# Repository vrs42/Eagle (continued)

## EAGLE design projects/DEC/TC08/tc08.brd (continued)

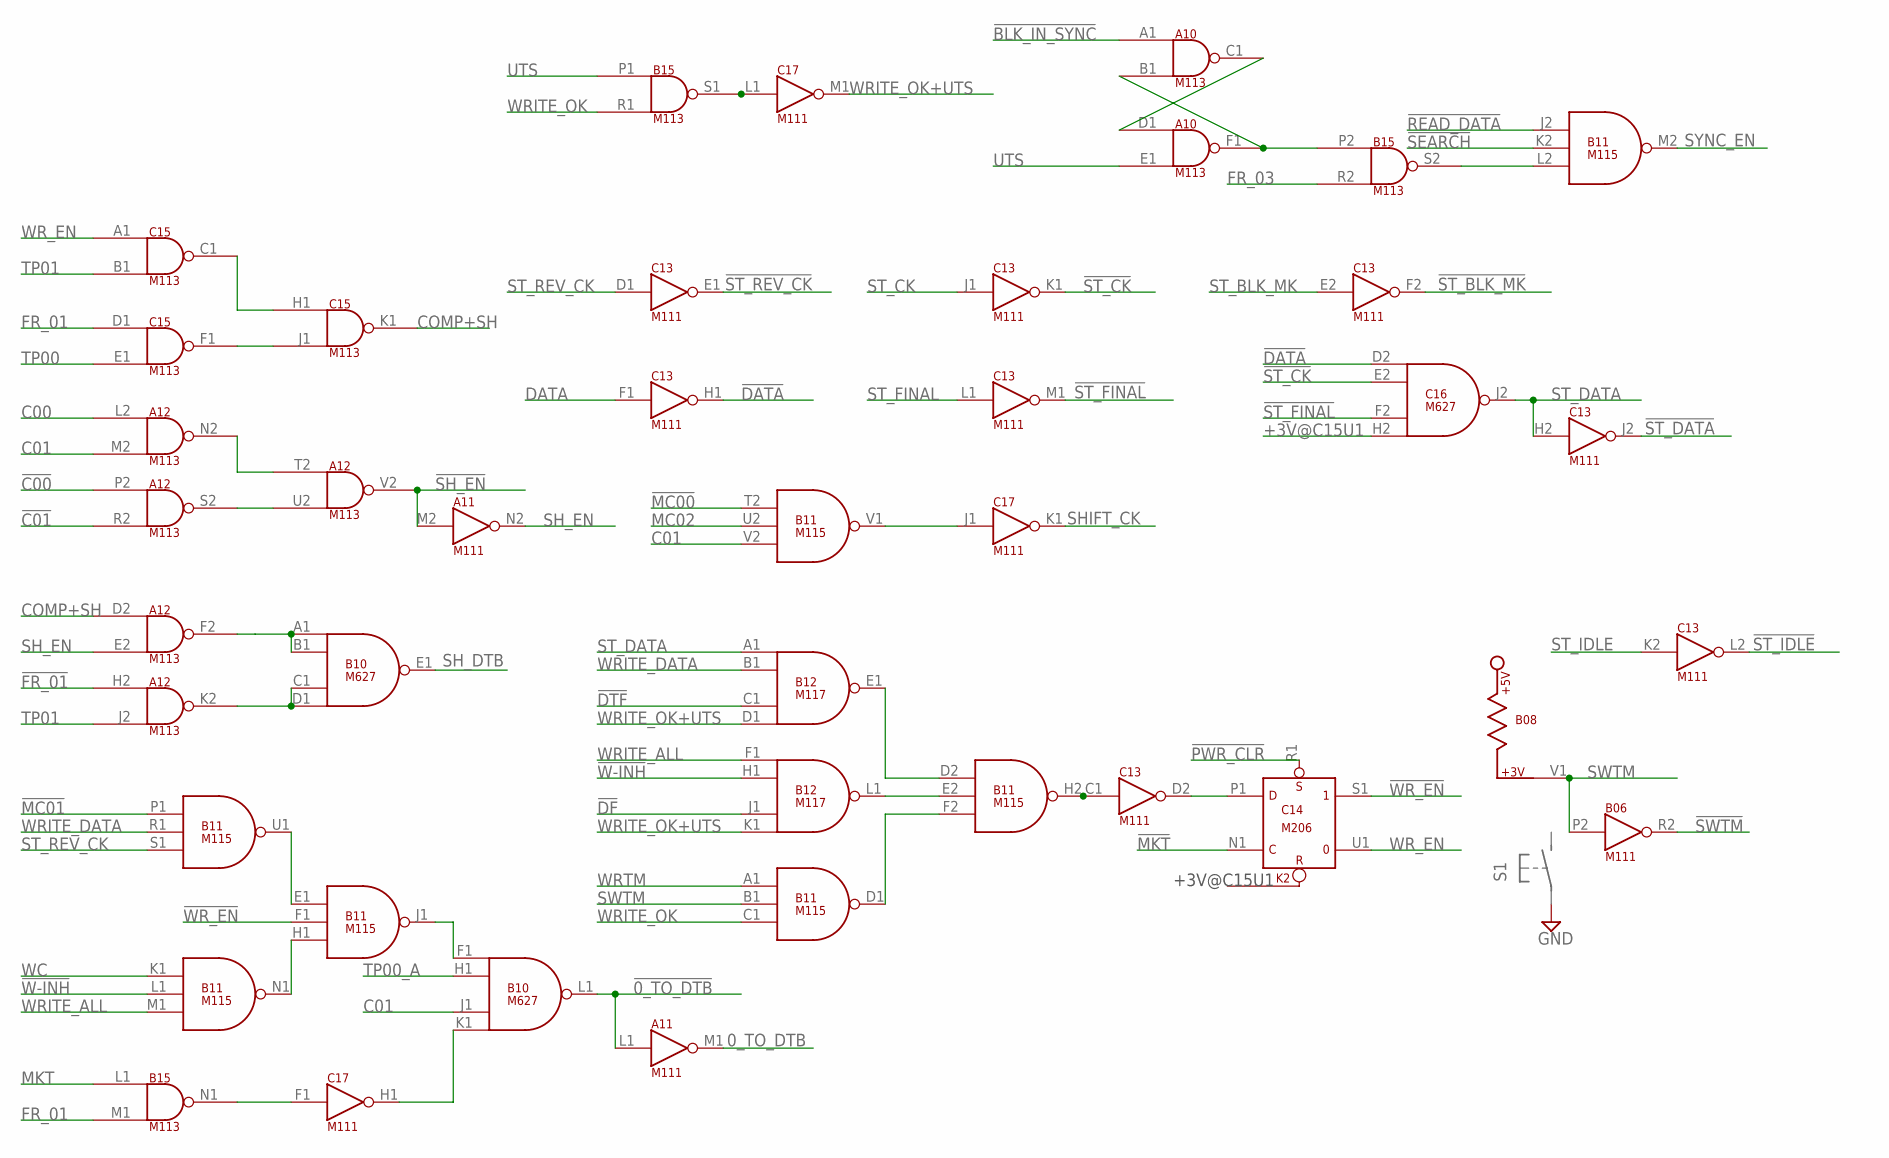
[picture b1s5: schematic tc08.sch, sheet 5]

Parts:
A10, A12: M113; H807
A11: M111; H807
B06: M111; H807
B08, B15: M113; H807
B10: M627; H807
B11: M115; H807
B12: M117; H807
C13, C17: M111; H807
C14: M206; H807
C15: M113; H807
C16: M627; H807

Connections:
0_TO_DTB: A11.M1 (OUT); also elsewhere on the board
!0_TO_DTB: A11.L1 (IN), B10.L1 (OUT); also elsewhere on the board
!BLK_IN_SYNC: A10.A1 (IN1); also elsewhere on the board
!C00: A12.P2 (IN1); also elsewhere on the board
!C01: A12.R2 (IN2); also elsewhere on the board
!DATA: C13.H1 (OUT), C16.D2 (IN1); also elsewhere on the board
!DF: B12.J1 (IN3); also elsewhere on the board
!DTF: B12.C1 (IN3); also elsewhere on the board
!FR_01: A12.H2 (IN1); also elsewhere on the board
!MC00: B11.T2 (IN1); also elsewhere on the board
!MC01: B11.P1 (IN1); also elsewhere on the board
!MKT: C14.N1 (C); also elsewhere on the board
!PWR_CLR: C14.R1 (S); also elsewhere on the board
!READ_DATA: B11.J2 (IN1); also elsewhere on the board
!SEARCH: B11.K2 (IN2); also elsewhere on the board
!SH_EN: A11.M2 (IN), A12.V2 (OUT); also elsewhere on the board
!ST_BLK_MK: C13.F2 (OUT); also elsewhere on the board
!ST_CK: C13.K1 (OUT), C16.E2 (IN2)
!ST_DATA: C13.J2 (OUT)
!ST_FINAL: C13.M1 (OUT), C16.F2 (IN3); also elsewhere on the board
!ST_IDLE: C13.L2 (OUT); also elsewhere on the board
!ST_REV_CK: C13.E1 (OUT)
!SWTM: B06.R2 (OUT); also elsewhere on the board
!W-INH: B11.L1 (IN2), B12.H1 (IN2); also elsewhere on the board
!WR_EN: B11.F1 (IN2), C14.S1 (1); also elsewhere on the board
+3V@C15U1: C16.H2 (IN4); also elsewhere on the board
C00: A12.L2 (IN1); also elsewhere on the board
C01: A12.M2 (IN2), B10.J1 (IN3), B11.V2 (IN3); also elsewhere on the board
COMP+SH: A12.D2 (IN1), C15.K1 (OUT); also elsewhere on the board
DATA: C13.F1 (IN); also elsewhere on the board
FR_01: B15.M1 (IN2), C15.D1 (IN1); also elsewhere on the board
FR_03: B15.R2 (IN2); also elsewhere on the board
GND: A10.C2 (GND), A10.T1 (GND), A11.C2 (GND), A11.T1 (GND), A12.C2 (GND), A12.T1 (GND), B06.C2 (GND), B06.T1 (GND), B08.C2 (GND), B08.T1 (GND), B10.C2 (GND), B10.T1 (GND), B11.C2 (GND), B11.T1 (GND), B12.C2 (GND), B12.T1 (GND), B15.C2 (GND), B15.T1 (GND), C13.C2 (GND), C13.T1 (GND), C14.C2 (GND), C14.T1 (GND), C15.C2 (GND), C15.T1 (GND), C16.C2 (GND), C16.T1 (GND), C17.C2 (GND), C17.T1 (GND); also elsewhere on the board
MC02: B11.U2 (IN2); also elsewhere on the board
MKT: B15.L1 (IN1); also elsewhere on the board
unnamed: B15.S1 (OUT), C17.L1 (IN)
unnamed: C13.D2 (OUT), C14.P1 (D)
unnamed: C15.C1 (OUT), C15.H1 (IN1)
unnamed: C15.F1 (OUT), C15.J1 (IN2)
unnamed: A12.N2 (OUT), A12.T2 (IN1)
unnamed: A12.S2 (OUT), A12.U2 (IN2)
unnamed: B11.H2 (OUT), C13.C1 (IN)
unnamed: B11.E2 (IN2), B12.L1 (OUT)
unnamed: B11.D2 (IN1), B12.E1 (OUT)
unnamed: B11.D1 (OUT), B11.F2 (IN3)
unnamed: A12.K2 (OUT), B10.C1 (IN3), B10.D1 (IN4)
unnamed: A12.F2 (OUT), B10.A1 (IN1), B10.B1 (IN2)
unnamed: B11.E1 (IN1), B11.U1 (OUT)
unnamed: B15.N1 (OUT), C17.F1 (IN)
unnamed: B11.H1 (IN3), B11.N1 (OUT)
unnamed: B10.F1 (IN1), B11.J1 (OUT)
unnamed: B10.K1 (IN4), C17.H1 (OUT)
unnamed: B11.V1 (OUT), C17.J1 (IN)
unnamed: A10.C1 (OUT), A10.D1 (IN1)
unnamed: A10.B1 (IN2), A10.F1 (OUT), B15.P2 (IN1)
unnamed: B11.L2 (IN3), B15.S2 (OUT)
SHIFT_CK: C17.K1 (OUT); also elsewhere on the board
SH_DTB: B10.E1 (OUT); also elsewhere on the board
SH_EN: A11.N2 (OUT), A12.E2 (IN2); also elsewhere on the board
ST_BLK_MK: C13.E2 (IN); also elsewhere on the board
ST_CK: C13.J1 (IN); also elsewhere on the board
ST_DATA: B12.A1 (IN1), C13.H2 (IN), C16.J2 (OUT)
ST_FINAL: C13.L1 (IN); also elsewhere on the board
ST_IDLE: C13.K2 (IN); also elsewhere on the board
ST_REV_CK: B11.S1 (IN3), C13.D1 (IN); also elsewhere on the board
SWTM: B06.P2 (IN), B08.V1, B11.B1 (IN2); also elsewhere on the board
SYNC_EN: B11.M2 (OUT); also elsewhere on the board
TP00: C15.E1 (IN2); also elsewhere on the board
TP00_A: B10.H1 (IN2); also elsewhere on the board
TP01: A12.J2 (IN2), C15.B1 (IN2); also elsewhere on the board
UTS: A10.E1 (IN2), B15.P1 (IN1); also elsewhere on the board
VCC: A10.A2 (VCC), A11.A2 (VCC), A12.A2 (VCC), B06.A2 (VCC), B08.A2 (VCC), B10.A2 (VCC), B11.A2 (VCC), B12.A2 (VCC), B15.A2 (VCC), C13.A2 (VCC), C14.A2 (VCC), C15.A2 (VCC), C16.A2 (VCC), C17.A2 (VCC); also elsewhere on the board
WC: B11.K1 (IN1); also elsewhere on the board
WRITE_ALL: B11.M1 (IN3), B12.F1 (IN1); also elsewhere on the board
WRITE_DATA: B11.R1 (IN2), B12.B1 (IN2); also elsewhere on the board
WRITE_OK: B11.C1 (IN3), B15.R1 (IN2); also elsewhere on the board
WRITE_OK+UTS: B12.D1 (IN4), B12.K1 (IN4), C17.M1 (OUT)
WRTM: B11.A1 (IN1); also elsewhere on the board
WR_EN: C14.U1 (0), C15.A1 (IN1); also elsewhere on the board

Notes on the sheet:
+3V@C15U1

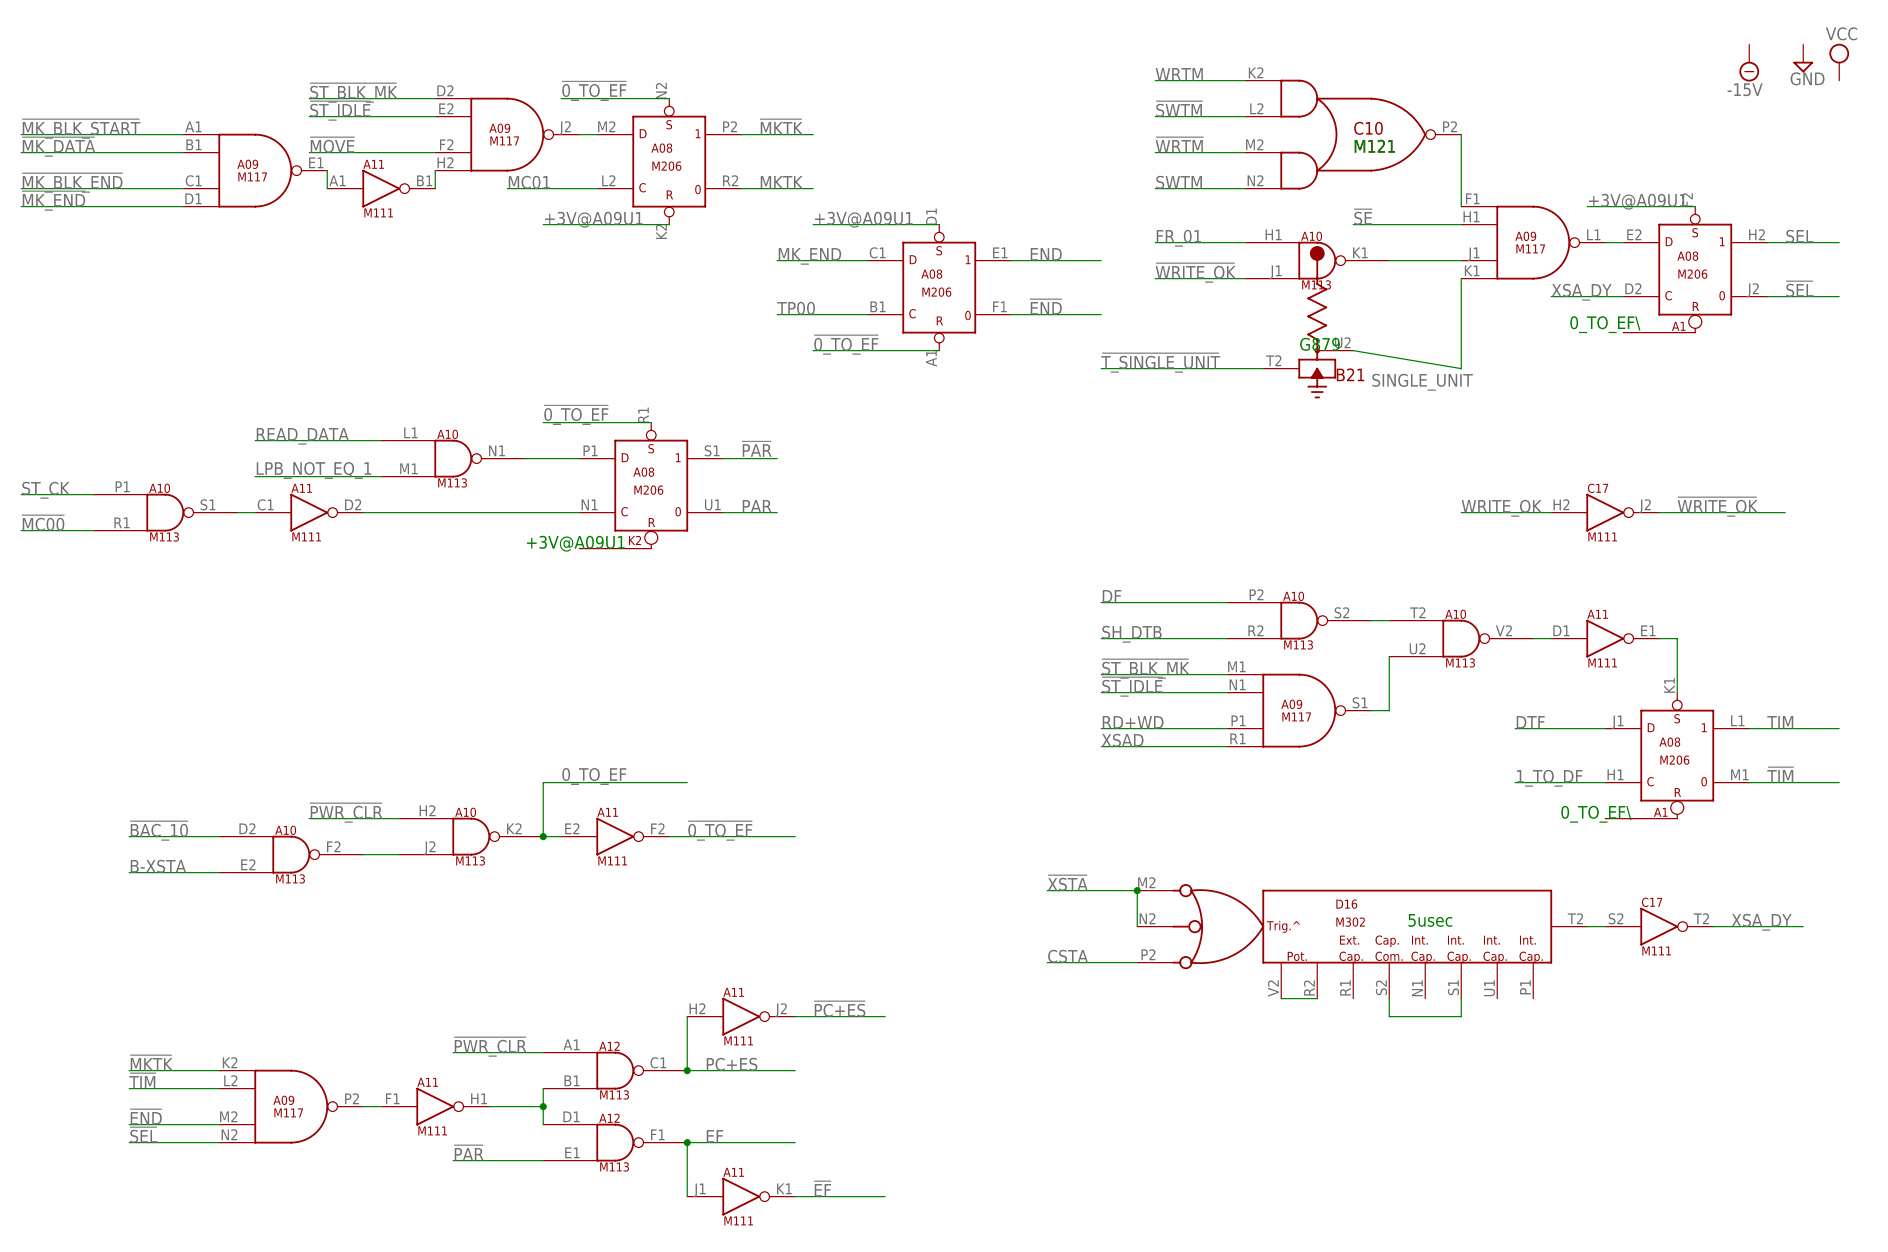
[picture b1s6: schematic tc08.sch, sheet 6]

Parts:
A08: M206; H807
A09: M117; H807
A10, A12: M113; H807
A11: M111; H807
B21: G879; H807
C10: M121; H807
C17: M111; H807
D16: M302; H807

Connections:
0_TO_EF: A10.K2 (OUT), A11.E2 (IN)
1_TO_DF: A08.H1 (C); also elsewhere on the board
!0_TO_EF: A08.A1 (R), A08.N2 (S), A08.R1 (S), A11.F2 (OUT)
!BAC_10: A10.D2 (IN1); also elsewhere on the board
!EF: A11.K1 (OUT); also elsewhere on the board
!END: A08.F1 (0), A09.M2 (IN3); also elsewhere on the board
!MC00: A10.R1 (IN2); also elsewhere on the board
!MKTK: A08.P2 (1), A09.K2 (IN1); also elsewhere on the board
!MK_BLK_END: A09.C1 (IN3); also elsewhere on the board
!MK_BLK_START: A09.A1 (IN1); also elsewhere on the board
!MK_DATA: A09.B1 (IN2); also elsewhere on the board
!MK_END: A09.D1 (IN4); also elsewhere on the board
!MOVE: A09.F2 (IN3); also elsewhere on the board
!PAR: A08.S1 (1), A12.E1 (IN2); also elsewhere on the board
!PC+ES: A11.J2 (OUT); also elsewhere on the board
!PWR_CLR: A10.H2 (IN1), A12.A1 (IN1); also elsewhere on the board
!SE: A09.H1 (IN2); also elsewhere on the board
!SEL: A08.J2 (0), A09.N2 (IN4); also elsewhere on the board
!ST_BLK_MK: A09.D2 (IN1), A09.M1 (IN1); also elsewhere on the board
!ST_IDLE: A09.E2 (IN2), A09.N1 (IN2); also elsewhere on the board
!SWTM: C10.L2 (IN1B); also elsewhere on the board
!TIM: A08.M1 (0), A09.L2 (IN2); also elsewhere on the board
!T_SINGLE_UNIT: B21.T2 (IN); also elsewhere on the board
!WRITE_OK: A10.J1 (IN2), C17.J2 (OUT)
!WRTM: C10.M2 (IN2A); also elsewhere on the board
!XSTA: D16.M2 (H2), D16.N2 (J2); also elsewhere on the board
+3V@A09U1: A08.D1 (S), A08.F2 (S), A08.K2 (R); also elsewhere on the board
-15V: B21.B2 (-15V); also elsewhere on the board
B-XSTA: A10.E2 (IN2); also elsewhere on the board
CSTA: D16.P2 (K2); also elsewhere on the board
DF: A10.P2 (IN1); also elsewhere on the board
DTF: A08.J1 (D); also elsewhere on the board
EF: A11.J1 (IN), A12.F1 (OUT); also elsewhere on the board
END: A08.E1 (1); also elsewhere on the board
FR_01: A10.H1 (IN1); also elsewhere on the board
GND: A08.C2 (GND), A08.T1 (GND), A09.C2 (GND), A09.T1 (GND), A10.C2 (GND), A10.T1 (GND), A11.C2 (GND), A11.T1 (GND), A12.C2 (GND), A12.T1 (GND), B21.C2 (GND), C10.C2 (GND), C10.T1 (GND), C17.C2 (GND), C17.T1 (GND), D16.C2 (GND), D16.T1 (GND); also elsewhere on the board
LPB_NOT_EQ_1: A10.M1 (IN2); also elsewhere on the board
MC01: A08.L2 (C); also elsewhere on the board
MKTK: A08.R2 (0); also elsewhere on the board
MK_END: A08.C1 (D); also elsewhere on the board
unnamed: C17.S2 (IN), D16.T2 (F2)
unnamed: A09.F1 (IN1), C10.P2 (OUT)
unnamed: A09.J1 (IN3), A10.K1 (OUT)
unnamed: A08.E2 (D), A09.L1 (OUT)
unnamed: A09.E1 (OUT), A11.A1 (IN)
unnamed: A09.H2 (IN4), A11.B1 (OUT)
unnamed: A08.M2 (D), A09.J2 (OUT)
unnamed: A10.S1 (OUT), A11.C1 (IN)
unnamed: A08.P1 (D), A10.N1 (OUT)
unnamed: A08.N1 (C), A11.D2 (OUT)
unnamed: A08.K1 (S), A11.E1 (OUT)
unnamed: A10.V2 (OUT), A11.D1 (IN)
unnamed: A09.S1 (OUT), A10.U2 (IN2)
unnamed: A10.S2 (OUT), A10.T2 (IN1)
unnamed: D16.S1 (H1), D16.S2 (L2)
unnamed: D16.R2 (E2), D16.V2 (D2)
unnamed: A10.F2 (OUT), A10.J2 (IN2)
unnamed: A09.P2 (OUT), A11.F1 (IN)
unnamed: A11.H1 (OUT), A12.B1 (IN2), A12.D1 (IN1)
PAR: A08.U1 (0); also elsewhere on the board
PC+ES: A11.H2 (IN), A12.C1 (OUT)
RD+WD: A09.P1 (IN3); also elsewhere on the board
READ_DATA: A10.L1 (IN1); also elsewhere on the board
SEL: A08.H2 (1); also elsewhere on the board
SH_DTB: A10.R2 (IN2); also elsewhere on the board
SINGLE_UNIT: A09.K1 (IN4), B21.U2 (OUT)
ST_CK: A10.P1 (IN1); also elsewhere on the board
SWTM: C10.N2 (IN2B); also elsewhere on the board
TIM: A08.L1 (1); also elsewhere on the board
TP00: A08.B1 (C); also elsewhere on the board
VCC: A08.A2 (VCC), A09.A2 (VCC), A10.A2 (VCC), A11.A2 (VCC), A12.A2 (VCC), B21.A2 (VCC), C10.A2 (VCC), C17.A2 (VCC), D16.A2 (VCC); also elsewhere on the board
WRITE_OK: C17.H2 (IN); also elsewhere on the board
WRTM: C10.K2 (IN1A); also elsewhere on the board
XSAD: A09.R1 (IN4); also elsewhere on the board
XSA_DY: A08.D2 (C), C17.T2 (OUT); also elsewhere on the board

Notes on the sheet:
G879
M121
5usec
+3V@A09U1
0_TO_EF\\

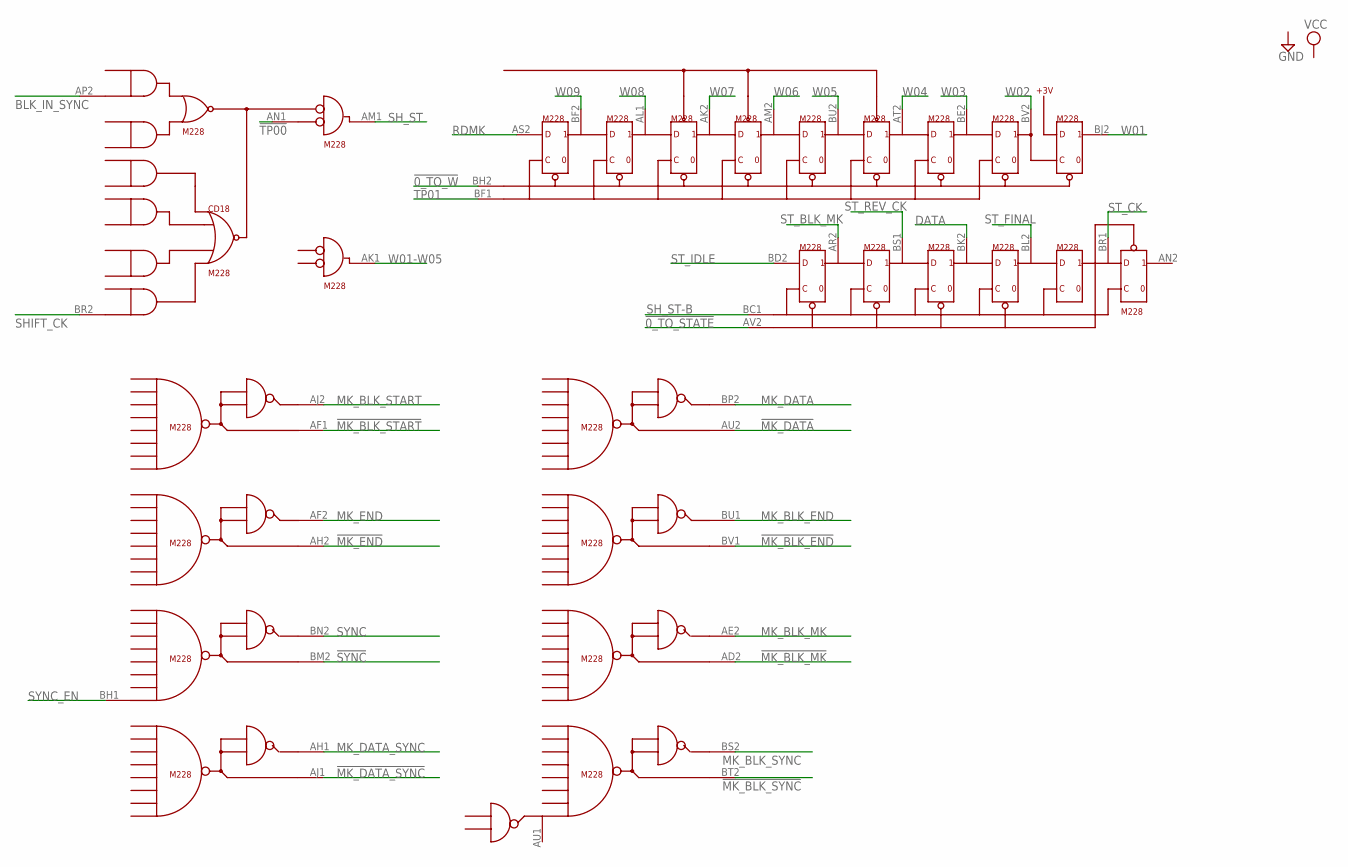
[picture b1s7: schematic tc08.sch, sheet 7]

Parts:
CD18: M228; H807-2

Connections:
!0_TO_STATE: CD18.AV2; also elsewhere on the board
!0_TO_W: CD18.BH2; also elsewhere on the board
!MK_BLK_END: CD18.BV1; also elsewhere on the board
!MK_BLK_MK: CD18.AD2
!MK_BLK_START: CD18.AF1; also elsewhere on the board
!MK_BLK_SYNC: CD18.BT2
!MK_DATA: CD18.AU2; also elsewhere on the board
!MK_DATA_SYNC: CD18.AJ1
!MK_END: CD18.AH2; also elsewhere on the board
!SYNC: CD18.BM2
!TP00: CD18.AN1; also elsewhere on the board
BLK_IN_SYNC: CD18.AP2; also elsewhere on the board
DATA: CD18.BK2; also elsewhere on the board
GND: CD18.AC2 (GND), CD18.AT1 (GND), CD18.BC2 (GND), CD18.BT1 (GND); also elsewhere on the board
MK_BLK_END: CD18.BU1; also elsewhere on the board
MK_BLK_MK: CD18.AE2; also elsewhere on the board
MK_BLK_START: CD18.AJ2
MK_BLK_SYNC: CD18.BS2
MK_DATA: CD18.BP2
MK_DATA_SYNC: CD18.AH1
MK_END: CD18.AF2; also elsewhere on the board
RDMK: CD18.AS2; also elsewhere on the board
SHIFT_CK: CD18.BR2; also elsewhere on the board
SH_ST: CD18.AM1; also elsewhere on the board
SH_ST-B: CD18.BC1; also elsewhere on the board
ST_BLK_MK: CD18.AR2; also elsewhere on the board
ST_CK: CD18.BR1; also elsewhere on the board
ST_FINAL: CD18.BL2; also elsewhere on the board
ST_IDLE: CD18.BD2; also elsewhere on the board
ST_REV_CK: CD18.BS1; also elsewhere on the board
SYNC: CD18.BN2; also elsewhere on the board
SYNC_EN: CD18.BH1; also elsewhere on the board
TP01: CD18.BF1; also elsewhere on the board
VCC: CD18.AA2 (VCC), CD18.BA2 (VCC); also elsewhere on the board
W01: CD18.BJ2; also elsewhere on the board
W01-W05: CD18.AK1
W02: CD18.BV2; also elsewhere on the board
W03: CD18.BE2; also elsewhere on the board
W04: CD18.AT2; also elsewhere on the board
W05: CD18.BU2; also elsewhere on the board
W06: CD18.AM2; also elsewhere on the board
W07: CD18.AK2; also elsewhere on the board
W08: CD18.AL1; also elsewhere on the board
W09: CD18.BF2; also elsewhere on the board

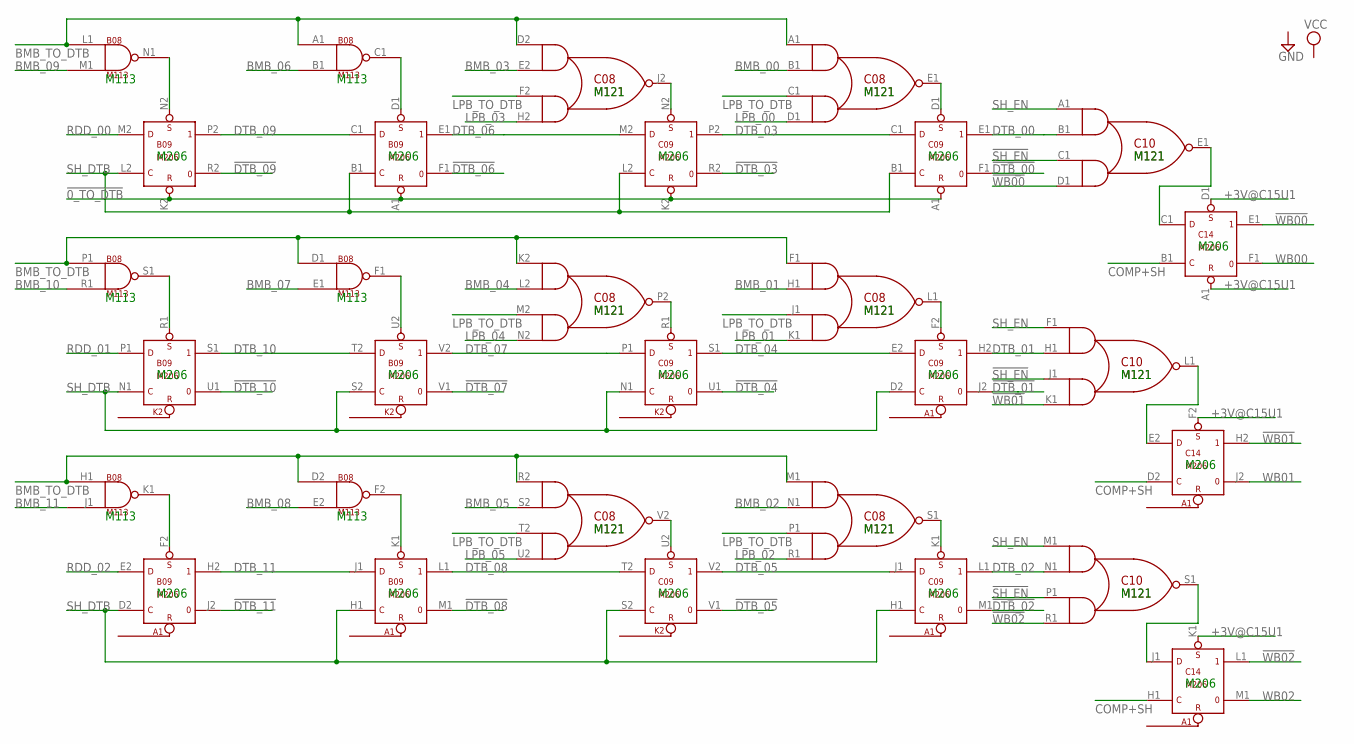
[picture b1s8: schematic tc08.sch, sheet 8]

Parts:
B08: M113; H807
B09: M206; H807
C08, C10: M121; H807
C09, C14: M206; H807

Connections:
!0_TO_DTB: B09.A1 (R), B09.K2 (R), C09.A1 (R), C09.K2 (R); also elsewhere on the board
!DTB_00: C09.F1 (0); also elsewhere on the board
!DTB_01: C09.J2 (0); also elsewhere on the board
!DTB_02: C09.M1 (0); also elsewhere on the board
!DTB_03: C09.R2 (0); also elsewhere on the board
!DTB_04: C09.U1 (0); also elsewhere on the board
!DTB_05: C09.V1 (0); also elsewhere on the board
!DTB_06: B09.F1 (0); also elsewhere on the board
!DTB_07: B09.V1 (0); also elsewhere on the board
!DTB_08: B09.M1 (0); also elsewhere on the board
!DTB_09: B09.R2 (0); also elsewhere on the board
!DTB_10: B09.U1 (0); also elsewhere on the board
!DTB_11: B09.J2 (0); also elsewhere on the board
!SH_EN: C10.C1 (IN2A), C10.J1 (IN2A), C10.P1 (IN2A); also elsewhere on the board
!WB00: C10.D1 (IN2B), C14.E1 (1); also elsewhere on the board
!WB01: C10.K1 (IN2B), C14.H2 (1); also elsewhere on the board
!WB02: C10.R1 (IN2B), C14.L1 (1); also elsewhere on the board
+3V@C15U1: C14.A1 (R), C14.D1 (S), C14.F2 (S), C14.K1 (S); also elsewhere on the board
BMB_00: C08.B1 (IN1B); also elsewhere on the board
BMB_01: C08.H1 (IN1B); also elsewhere on the board
BMB_02: C08.N1 (IN1B); also elsewhere on the board
BMB_03: C08.E2 (IN1B); also elsewhere on the board
BMB_04: C08.L2 (IN1B); also elsewhere on the board
BMB_05: C08.S2 (IN1B); also elsewhere on the board
BMB_06: B08.B1 (IN2); also elsewhere on the board
BMB_07: B08.E1 (IN2); also elsewhere on the board
BMB_08: B08.E2 (IN2); also elsewhere on the board
BMB_09: B08.M1 (IN2); also elsewhere on the board
BMB_10: B08.R1 (IN2); also elsewhere on the board
BMB_11: B08.J1 (IN2); also elsewhere on the board
BMB_TO_DTB: B08.A1 (IN1), B08.D1 (IN1), B08.D2 (IN1), B08.H1 (IN1), B08.L1 (IN1), B08.P1 (IN1), C08.A1 (IN1A), C08.D2 (IN1A), C08.F1 (IN1A), C08.K2 (IN1A), C08.M1 (IN1A), C08.R2 (IN1A); also elsewhere on the board
COMP+SH: C14.B1 (C), C14.D2 (C), C14.H1 (C); also elsewhere on the board
DTB_00: C09.E1 (1), C10.B1 (IN1B); also elsewhere on the board
DTB_01: C09.H2 (1), C10.H1 (IN1B); also elsewhere on the board
DTB_02: C09.L1 (1), C10.N1 (IN1B); also elsewhere on the board
DTB_03: C09.C1 (D), C09.P2 (1); also elsewhere on the board
DTB_04: C09.E2 (D), C09.S1 (1); also elsewhere on the board
DTB_05: C09.J1 (D), C09.V2 (1); also elsewhere on the board
DTB_06: B09.E1 (1), C09.M2 (D); also elsewhere on the board
DTB_07: B09.V2 (1), C09.P1 (D); also elsewhere on the board
DTB_08: B09.L1 (1), C09.T2 (D); also elsewhere on the board
DTB_09: B09.C1 (D), B09.P2 (1); also elsewhere on the board
DTB_10: B09.S1 (1), B09.T2 (D); also elsewhere on the board
DTB_11: B09.H2 (1), B09.J1 (D); also elsewhere on the board
GND: B08.C2 (GND), B08.T1 (GND), B09.C2 (GND), B09.T1 (GND), C08.C2 (GND), C08.T1 (GND), C09.C2 (GND), C09.T1 (GND), C10.C2 (GND), C10.T1 (GND), C14.C2 (GND), C14.T1 (GND); also elsewhere on the board
LPB_00: C08.D1 (IN2B); also elsewhere on the board
LPB_01: C08.K1 (IN2B); also elsewhere on the board
LPB_02: C08.R1 (IN2B); also elsewhere on the board
LPB_03: C08.H2 (IN2B); also elsewhere on the board
LPB_04: C08.N2 (IN2B); also elsewhere on the board
LPB_05: C08.U2 (IN2B); also elsewhere on the board
LPB_TO_DTB: C08.C1 (IN2A), C08.F2 (IN2A), C08.J1 (IN2A), C08.M2 (IN2A), C08.P1 (IN2A), C08.T2 (IN2A); also elsewhere on the board
unnamed: B08.N1 (OUT), B09.N2 (S)
unnamed: B08.S1 (OUT), B09.R1 (S)
unnamed: B08.K1 (OUT), B09.F2 (S)
unnamed: B08.C1 (OUT), B09.D1 (S)
unnamed: C08.J2 (OUT), C09.N2 (S)
unnamed: B08.F1 (OUT), B09.U2 (S)
unnamed: B08.F2 (OUT), B09.K1 (S)
unnamed: C08.V2 (OUT), C09.U2 (S)
unnamed: C08.P2 (OUT), C09.R1 (S)
unnamed: C08.E1 (OUT), C09.D1 (S)
unnamed: C08.L1 (OUT), C09.F2 (S)
unnamed: C08.S1 (OUT), C09.K1 (S)
unnamed: C10.L1 (OUT), C14.E2 (D)
unnamed: C10.E1 (OUT), C14.C1 (D)
unnamed: C10.S1 (OUT), C14.J1 (D)
RDD_00: B09.M2 (D); also elsewhere on the board
RDD_01: B09.P1 (D); also elsewhere on the board
RDD_02: B09.E2 (D); also elsewhere on the board
SH_DTB: B09.B1 (C), B09.D2 (C), B09.H1 (C), B09.L2 (C), B09.N1 (C), B09.S2 (C), C09.B1 (C), C09.D2 (C), C09.H1 (C), C09.L2 (C), C09.N1 (C), C09.S2 (C); also elsewhere on the board
SH_EN: C10.A1 (IN1A), C10.F1 (IN1A), C10.M1 (IN1A); also elsewhere on the board
VCC: B08.A2 (VCC), B09.A2 (VCC), C08.A2 (VCC), C09.A2 (VCC), C10.A2 (VCC), C14.A2 (VCC); also elsewhere on the board
WB00: C14.F1 (0); also elsewhere on the board
WB01: C14.J2 (0); also elsewhere on the board
WB02: C14.M1 (0); also elsewhere on the board

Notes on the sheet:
M206
M121
M113

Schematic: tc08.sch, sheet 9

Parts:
A09: M117; H807
A11: M111; H807
C10: M121; H807
C11, C15: M113; H807
C12: M115; H807
C13, C17: M111; H807
D08: M207; H807
D09: M121; H807
D10: M119; H807
D12: M627; H807

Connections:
!0_TO_LPB: D08.A1, D08.K2, D12.J2 (OUT)
!C00: C15.J2 (IN2); also elsewhere on the board
!C01: C12.F2 (IN3); also elsewhere on the board
!LPB_00: D08.F1, D10.M1 (IN1)
!LPB_01: D08.M1, D10.N1 (IN2)
!LPB_02: D08.U1, D10.P1 (IN3)
!LPB_03: D08.J2, D10.R1 (IN4)
!LPB_04: D08.R2, D10.R2 (IN5)
!LPB_05: D08.V1, D10.S2 (IN6), D10.T2 (IN7), D10.U2 (IN8)
!WR_EN: C11.H2 (IN1), C15.D2 (IN1), C15.H2 (IN1); also elsewhere on the board
C00: C15.E2 (IN2); also elsewhere on the board
DTB_00: D09.D2 (IN1A); also elsewhere on the board
DTB_01: D09.K2 (IN1A); also elsewhere on the board
DTB_02: D09.R2 (IN1A); also elsewhere on the board
GND: A09.C2 (GND), A09.T1 (GND), A11.C2 (GND), A11.T1 (GND), C10.C2 (GND), C10.T1 (GND), C11.C2 (GND), C11.T1 (GND), C12.C2 (GND), C12.T1 (GND), C13.C2 (GND), C13.T1 (GND), C15.C2 (GND), C15.T1 (GND), C17.C2 (GND), C17.T1 (GND), D08.C2 (GND), D08.T1 (GND), D09.C2 (GND), D09.T1 (GND), D10.C2 (GND), D10.T1 (GND), D12.C2 (GND), D12.T1 (GND); also elsewhere on the board
LPB_00: D08.E1; also elsewhere on the board
LPB_01: D08.L1; also elsewhere on the board
LPB_02: D08.S1; also elsewhere on the board
LPB_03: D08.H2; also elsewhere on the board
LPB_04: D08.P2; also elsewhere on the board
LPB_05: D08.V2; also elsewhere on the board
LPB_NOT_EQ_1: D10.V2 (OUT); also elsewhere on the board
LPB_TO_DTB: A11.T2 (OUT); also elsewhere on the board
MC02: D12.D2 (IN1), D12.E2 (IN2); also elsewhere on the board
MKT: C15.L2 (IN1); also elsewhere on the board
MK_BLK_END: A09.T2 (IN3); also elsewhere on the board
unnamed: D08.C1, D08.D1, D09.E1 (OUT)
unnamed: D08.E2, D08.F2, D09.J2 (OUT)
unnamed: D08.J1, D08.K1, D09.L1 (OUT)
unnamed: D08.P1, D08.R1, D09.S1 (OUT)
unnamed: D08.T2, D08.U2, D09.V2 (OUT)
unnamed: D08.M2, D08.N2, D09.P2 (OUT)
unnamed: C17.U1 (OUT), D08.D2, D08.L2, D08.S2
unnamed: C17.N2 (OUT), D08.B1, D08.H1, D08.N1
unnamed: C10.J2 (OUT), C17.M2 (IN)
unnamed: C10.V2 (OUT), C17.V1 (IN)
unnamed: A09.U2 (IN4), C17.R2 (OUT)
unnamed: A09.V2 (OUT), A11.S2 (IN)
unnamed: C15.N2 (OUT), C17.P2 (IN)
unnamed: C13.S2 (IN), C15.K2 (OUT)
unnamed: C12.H2 (OUT), D12.M2 (IN3), D12.N2 (IN4)
unnamed: C11.K2 (OUT), D12.K2 (IN1), D12.L2 (IN2)
unnamed: C13.P2 (IN), C15.F2 (OUT)
RDD_00: D09.C1 (IN2A), D09.F2 (IN2A); also elsewhere on the board
RDD_01: D09.J1 (IN2A), D09.M2 (IN2A); also elsewhere on the board
RDD_02: D09.P1 (IN2A), D09.T2 (IN2A); also elsewhere on the board
RD_EN_LPB_00-02: C10.D2 (IN1A), C13.T2 (OUT), D09.D1 (IN2B), D09.K1 (IN2B), D09.R1 (IN2B)
RD_EN_LPB_03-05: C10.R2 (IN1A), C13.R2 (OUT), D09.H2 (IN2B), D09.N2 (IN2B), D09.U2 (IN2B)
ST_FINAL: A09.S2 (IN2); also elsewhere on the board
ST_REV_CK: D12.F2 (IN3), D12.H2 (IN4); also elsewhere on the board
TP00_A: C12.E2 (IN2); also elsewhere on the board
TP01: C11.J2 (IN2); also elsewhere on the board
TP01_A: C15.M2 (IN2); also elsewhere on the board
VCC: A09.A2 (VCC), A11.A2 (VCC), C10.A2 (VCC), C11.A2 (VCC), C12.A2 (VCC), C13.A2 (VCC), C15.A2 (VCC), C17.A2 (VCC), D08.A2 (VCC), D09.A2 (VCC), D10.A2 (VCC), D12.A2 (VCC); also elsewhere on the board
WB00: D09.A1 (IN1A); also elsewhere on the board
WB01: D09.F1 (IN1A); also elsewhere on the board
WB02: D09.M1 (IN1A); also elsewhere on the board
WRITE_DATA: A09.R2 (IN1); also elsewhere on the board
WR_EN: C10.H2 (IN2B), C10.U2 (IN2B), C12.D2 (IN1), D09.B1 (IN1B), D09.E2 (IN1B), D09.H1 (IN1B), D09.L2 (IN1B), D09.N1 (IN1B), D09.S2 (IN1B); also elsewhere on the board
XOR_TO_LPB: C10.E2 (IN1B), C10.F2 (IN2A), C10.S2 (IN1B), C10.T2 (IN2A), D12.P2 (OUT)

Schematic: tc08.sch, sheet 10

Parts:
A18, A20, A21: G888; H807
AB01: G821; H807-2
AB19: W032; H807-2
B06: M111; H807
B18, B20: G888; H807
C06: M111; H807

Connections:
!BAC_00: B06.A1 (IN); also elsewhere on the board
!BAC_01: B06.D1 (IN); also elsewhere on the board
!BAC_02: B06.F1 (IN); also elsewhere on the board
!BAC_03: B06.J1 (IN); also elsewhere on the board
!BAC_04: B06.L1 (IN); also elsewhere on the board
!BAC_05: B06.N1 (IN); also elsewhere on the board
!BAC_06: B06.R1 (IN); also elsewhere on the board
!BAC_07: B06.V1 (IN); also elsewhere on the board
!BAC_08: B06.C1 (IN); also elsewhere on the board
!BAC_09: B06.E2 (IN); also elsewhere on the board
!BAC_10: B06.H2 (IN); also elsewhere on the board
!BAC_11: B06.K2 (IN); also elsewhere on the board
!BMB_00: C06.A1 (IN); also elsewhere on the board
!BMB_01: C06.D1 (IN); also elsewhere on the board
!BMB_02: C06.F1 (IN); also elsewhere on the board
!BMB_03: C06.J1 (IN); also elsewhere on the board
!BMB_04: C06.L1 (IN); also elsewhere on the board
!BMB_05: C06.N1 (IN); also elsewhere on the board
!BMB_06: C06.R1 (IN); also elsewhere on the board
!BMB_07: C06.V1 (IN); also elsewhere on the board
!BMB_08: C06.C1 (IN); also elsewhere on the board
!BMB_09: C06.E2 (IN); also elsewhere on the board
!BMB_10: C06.H2 (IN); also elsewhere on the board
!BMB_11: C06.K2 (IN); also elsewhere on the board
!CK00: A18.N2; also elsewhere on the board
!RDD_00: A21.V2
!RDD_01: B20.V2
!RDD_02: A20.V2
!RDMK: B18.V2
!T_TRK: A18.V2; also elsewhere on the board
!WB00: A21.P2, B18.P2; also elsewhere on the board
!WB01: B20.P2; also elsewhere on the board
!WB02: A20.P2; also elsewhere on the board
+11V: AB01.BM2 (+11V)
-15V: A18.B2 (-15V), A20.B2 (-15V), A21.B2 (-15V), AB01.AB2 (-15V), AB01.AE2 (-15V), AB01.AF2 (-15V), B18.B2 (-15V), B20.B2 (-15V); also elsewhere on the board
BAC_00: B06.B1 (OUT); also elsewhere on the board
BAC_01: B06.E1 (OUT); also elsewhere on the board
BAC_02: B06.H1 (OUT); also elsewhere on the board
BAC_03: B06.K1 (OUT); also elsewhere on the board
BAC_04: B06.M1 (OUT); also elsewhere on the board
BAC_05: B06.P1 (OUT); also elsewhere on the board
BAC_06: B06.S1 (OUT); also elsewhere on the board
BAC_07: B06.U1 (OUT); also elsewhere on the board
BAC_08: B06.D2 (OUT); also elsewhere on the board
BAC_09: B06.F2 (OUT); also elsewhere on the board
BAC_10: B06.J2 (OUT)
BAC_11: B06.L2 (OUT)
BMB_00: C06.B1 (OUT); also elsewhere on the board
BMB_01: C06.E1 (OUT); also elsewhere on the board
BMB_02: C06.H1 (OUT); also elsewhere on the board
BMB_03: C06.K1 (OUT); also elsewhere on the board
BMB_04: C06.M1 (OUT); also elsewhere on the board
BMB_05: C06.P1 (OUT); also elsewhere on the board
BMB_06: C06.S1 (OUT); also elsewhere on the board
BMB_07: C06.U1 (OUT); also elsewhere on the board
BMB_08: C06.D2 (OUT); also elsewhere on the board
BMB_09: C06.F2 (OUT); also elsewhere on the board
BMB_10: C06.J2 (OUT); also elsewhere on the board
BMB_11: C06.L2 (OUT); also elsewhere on the board
CK00: A18.P2; also elsewhere on the board
GND: A18.C2 (GND), A20.C2 (GND), A21.C2 (GND), AB01.AC2 (GND), AB01.AH2 (GND), AB01.AK2 (GND), AB01.AL2 (GND), AB01.AT1 (GND), AB01.BC2 (GND), AB01.BD2 (GND), AB01.BH2 (GND), AB01.BK2 (GND), AB01.BL2 (GND), AB01.BT1 (GND), AB19.AC2 (GND), AB19.AJ2, AB19.AK2 (GND), AB19.AR2, AB19.AS2 (GND), AB19.AT2 (GND), AB19.AU2, AB19.BE2 (GND), AB19.BF2, AB19.BL2 (GND), AB19.BM2, B06.C2 (GND), B06.T1 (GND), B18.C2 (GND), B20.C2 (GND), C06.C2 (GND), C06.T1 (GND); also elsewhere on the board
unnamed: A18.D2, A18.J2, AB19.AF2
unnamed: A18.E2, A18.K2, AB19.AH2
unnamed: AB19.AN2, B18.D2, B18.J2
unnamed: AB19.AP2, B18.E2, B18.K2
unnamed: A20.D2, A20.J2, AB19.AV2
unnamed: A20.E2, A20.K2, AB19.BD2
unnamed: AB19.BH2, B20.D2, B20.J2
unnamed: AB19.BJ2, B20.E2, B20.K2
unnamed: A21.D2, A21.J2, AB19.BN2
unnamed: A21.E2, A21.K2, AB19.BP2
RDD_00: A21.U2; also elsewhere on the board
RDD_01: B20.U2; also elsewhere on the board
RDD_02: A20.U2; also elsewhere on the board
RDMK: B18.U2; also elsewhere on the board
TM_EN: A18.R2, B18.R2; also elsewhere on the board
T_TRK: A18.U2; also elsewhere on the board
VCC: A18.A2 (VCC), A20.A2 (VCC), A21.A2 (VCC), AB01.AA2 (VCC), AB01.AB1 (VCC), AB01.AC1 (VCC), AB01.AD1 (VCC), AB01.AE1 (VCC), AB01.AF1 (VCC), AB01.AH1 (VCC), AB01.AJ1 (VCC), AB01.AK1 (VCC), AB01.AL1 (VCC), AB01.BA2 (VCC), AB01.BB1 (VCC), AB01.BC1 (VCC), AB01.BD1 (VCC), AB01.BE1 (VCC), B06.A2 (VCC), B18.A2 (VCC), B20.A2 (VCC), C06.A2 (VCC); also elsewhere on the board
WB00: A21.N2, B18.N2; also elsewhere on the board
WB01: B20.N2; also elsewhere on the board
WB02: A20.N2; also elsewhere on the board
WR_EN: A20.R2, A21.R2, B20.R2; also elsewhere on the board
